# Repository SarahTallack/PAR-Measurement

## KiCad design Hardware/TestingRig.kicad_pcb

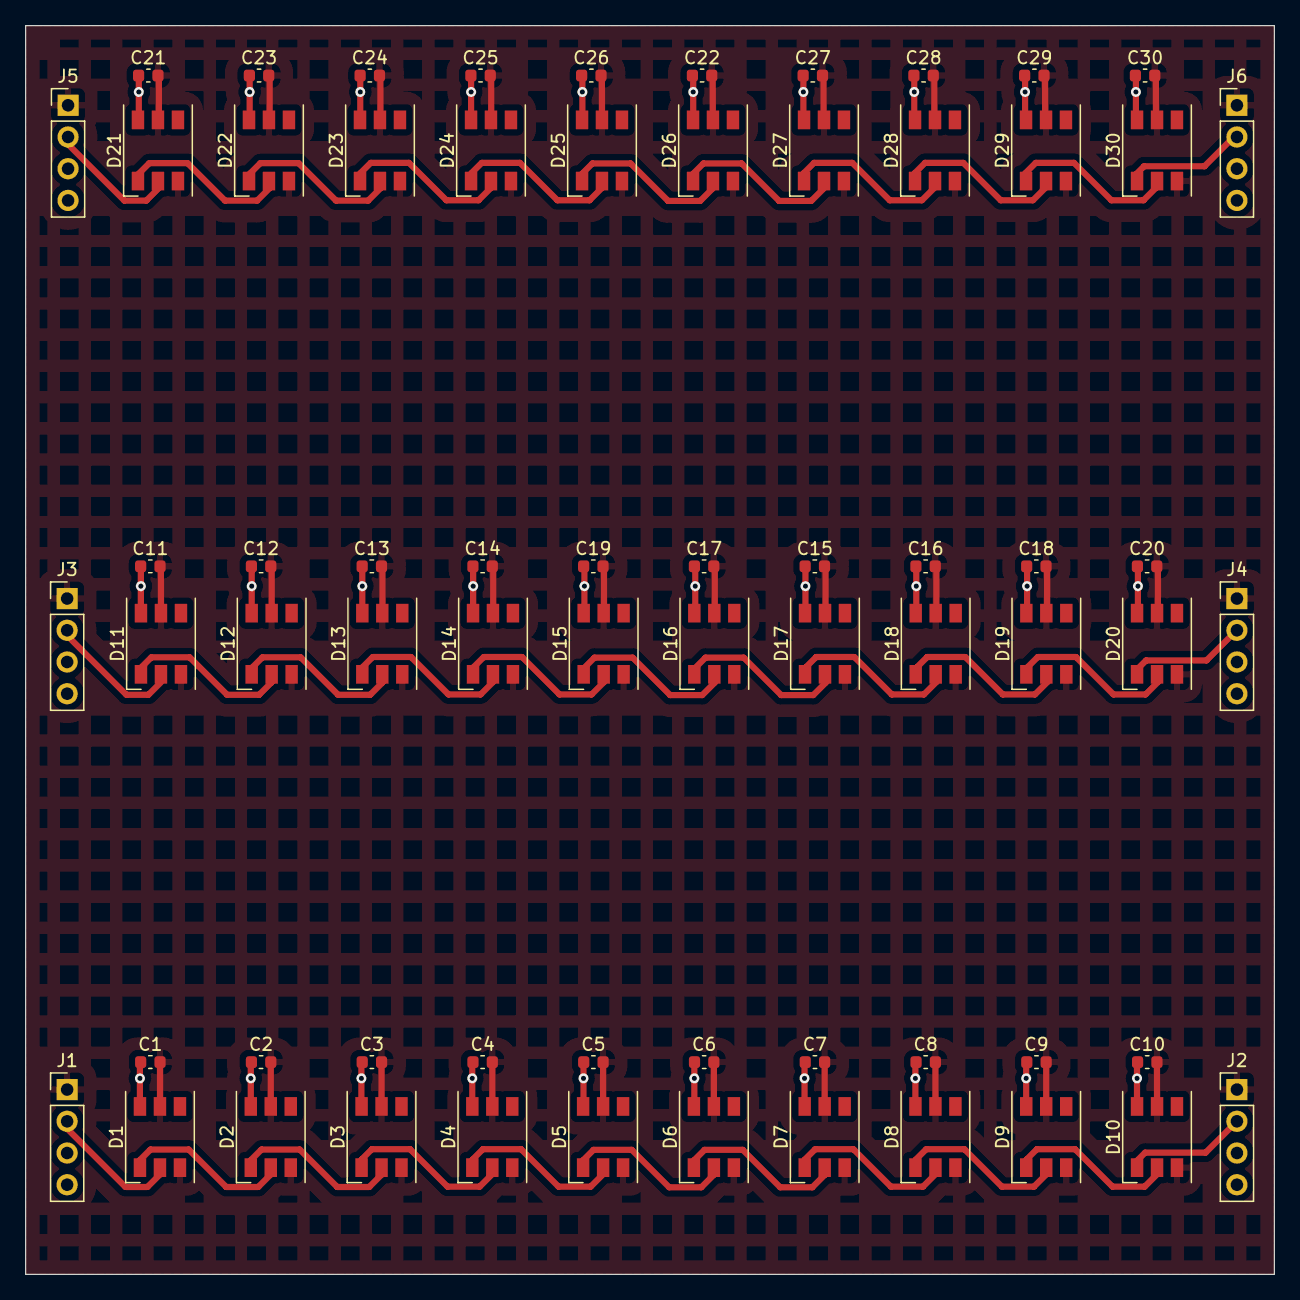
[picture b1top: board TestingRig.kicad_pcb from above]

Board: 2 copper layers, 100.0 x 100.0 mm, 66 parts (0 on the bottom side), 35 nets.

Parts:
C1, C2, C3, C4, C5, C6, C7, C8, C9, C10, C11, C12, C13, C14, C15, C16, C17, C18, C19, C20, C21, C22, C23, C24, C25, C26, C27, C28, C29, C30: 100n; C_0603_1608Metric
D1, D2, D3, D4, D5, D6, D7, D8, D9, D10, D11, D12, D13, D14, D15, D16, D17, D18, D19, D20, D21, D22, D23, D24, D25, D26, D27, D28, D29, D30: WS2812; LED_WS2812_PLCC6_5.0x5.0mm_P1.6mm
J1, J2, J3, J4, J5, J6: Conn_01x04_Pin; PinHeader_1x04_P2.54mm_Vertical

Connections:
/+5V: C1.2, C2.2, C3.2, C4.2, C5.2, C6.2, C7.2, C8.2, C9.2, C10.2, C11.2, C12.2, C13.2, C14.2, C15.2, C16.2, C17.2, C18.2, C19.2, C20.2, C21.2, C22.2, C23.2, C24.2, C25.2, C26.2, C27.2, C28.2, C29.2, C30.2, D1.3 (VCC), D1.5 (VDD), D2.3 (VCC), D2.5 (VDD), D3.3 (VCC), D3.5 (VDD), D4.3 (VCC), D4.5 (VDD), D5.3 (VCC), D5.5 (VDD), D6.3 (VCC), D6.5 (VDD), D7.3 (VCC), D7.5 (VDD), D8.3 (VCC), D8.5 (VDD), D9.3 (VCC), D9.5 (VDD), D10.3 (VCC), D10.5 (VDD), D11.3 (VCC), D11.5 (VDD), D12.3 (VCC), D12.5 (VDD), D13.3 (VCC), D13.5 (VDD), D14.3 (VCC), D14.5 (VDD), D15.3 (VCC), D15.5 (VDD), D16.3 (VCC), D16.5 (VDD), D17.3 (VCC), D17.5 (VDD), D18.3 (VCC), D18.5 (VDD), D19.3 (VCC), D19.5 (VDD), D20.3 (VCC), D20.5 (VDD), D21.3 (VCC), D21.5 (VDD), D22.3 (VCC), D22.5 (VDD), D23.3 (VCC), D23.5 (VDD), D24.3 (VCC), D24.5 (VDD), D25.3 (VCC), D25.5 (VDD), D26.3 (VCC), D26.5 (VDD), D27.3 (VCC), D27.5 (VDD), D28.3 (VCC), D28.5 (VDD), D29.3 (VCC), D29.5 (VDD), D30.3 (VCC), D30.5 (VDD), J1.1, J2.1, J3.1, J4.1, J5.1, J6.1
/Din1: D1.2 (DIN), J1.2
/Din11: D11.2 (DIN), J3.2
/Din21: D21.2 (DIN), J5.2
/Dout1: D1.1 (DOUT), D2.2 (DIN)
/Dout2: D2.1 (DOUT), D3.2 (DIN)
/Dout3: D3.1 (DOUT), D4.2 (DIN)
/Dout4: D4.1 (DOUT), D5.2 (DIN)
/Dout5: D5.1 (DOUT), D6.2 (DIN)
/Dout6: D6.1 (DOUT), D7.2 (DIN)
/Dout7: D7.1 (DOUT), D8.2 (DIN)
/Dout8: D8.1 (DOUT), D9.2 (DIN)
/Dout9: D9.1 (DOUT), D10.2 (DIN)
/Dout10: D10.1 (DOUT), J2.2
/Dout11: D11.1 (DOUT), D12.2 (DIN)
/Dout12: D12.1 (DOUT), D13.2 (DIN)
/Dout13: D13.1 (DOUT), D14.2 (DIN)
/Dout14: D14.1 (DOUT), D15.2 (DIN)
/Dout15: D15.1 (DOUT), D16.2 (DIN)
/Dout16: D16.1 (DOUT), D17.2 (DIN)
/Dout17: D17.1 (DOUT), D18.2 (DIN)
/Dout18: D18.1 (DOUT), D19.2 (DIN)
/Dout19: D19.1 (DOUT), D20.2 (DIN)
/Dout20: D20.1 (DOUT), J4.2
/Dout21: D21.1 (DOUT), D22.2 (DIN)
/Dout22: D22.1 (DOUT), D23.2 (DIN)
/Dout23: D23.1 (DOUT), D24.2 (DIN)
/Dout24: D24.1 (DOUT), D25.2 (DIN)
/Dout25: D25.1 (DOUT), D26.2 (DIN)
/Dout26: D26.1 (DOUT), D27.2 (DIN)
/Dout27: D27.1 (DOUT), D28.2 (DIN)
/Dout28: D28.1 (DOUT), D29.2 (DIN)
/Dout29: D29.1 (DOUT), D30.2 (DIN)
/Dout30: D30.1 (DOUT), J6.2
GND: C1.1, C2.1, C3.1, C4.1, C5.1, C6.1, C7.1, C8.1, C9.1, C10.1, C11.1, C12.1, C13.1, C14.1, C15.1, C16.1, C17.1, C18.1, C19.1, C20.1, C21.1, C22.1, C23.1, C24.1, C25.1, C26.1, C27.1, C28.1, C29.1, C30.1, D1.6 (VSS), D2.6 (VSS), D3.6 (VSS), D4.6 (VSS), D5.6 (VSS), D6.6 (VSS), D7.6 (VSS), D8.6 (VSS), D9.6 (VSS), D10.6 (VSS), D11.6 (VSS), D12.6 (VSS), D13.6 (VSS), D14.6 (VSS), D15.6 (VSS), D16.6 (VSS), D17.6 (VSS), D18.6 (VSS), D19.6 (VSS), D20.6 (VSS), D21.6 (VSS), D22.6 (VSS), D23.6 (VSS), D24.6 (VSS), D25.6 (VSS), D26.6 (VSS), D27.6 (VSS), D28.6 (VSS), D29.6 (VSS), D30.6 (VSS), J1.3, J1.4, J2.3, J2.4, J3.3, J3.4, J4.3, J4.4, J5.3, J5.4, J6.3, J6.4

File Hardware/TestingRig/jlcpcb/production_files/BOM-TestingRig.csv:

Comment,Designator,Footprint,LCSC
WS2812,"D1,D10,D11,D12,D13,D14,D15,D16,D17,D18,D19,D2,D20,D21,D22,D23,D24,D25,D26,D27,D3,D4,D5,D6,D7,D8,D9",LED_WS2812_PLCC6_5.0x5.0mm_P1.6mm,C2843785
100n,"C1,C10,C11,C12,C13,C14,C15,C16,C17,C18,C19,C2,C20,C21,C22,C23,C24,C25,C26,C27,C3,C4,C5,C6,C7,C8,C9",C_0603_1608Metric,C49678
